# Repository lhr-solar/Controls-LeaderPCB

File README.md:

# Electronics : SCH/PCB
Contains all schematics and PCB files for the electrical system. Some teams may use the Solar Google Drive to upload their files.

------ 2025 Daybreak Controls Leaderboard ------
Purpose: Run main Controls code and interface with the motor controller and other systems through CAN.
Mouser link BOM: <to come>
List of components taking up volume outside of board dimensions
- Molex connectors along the entire perimeter (and one slightly inside) of the board
- Pin headers on the board
LEDs:
- Cruise controls is on
- Controls has a fault
- BPS has sent a fault
- Motor controller sent a fault
- Array precharge bypass contactor pin is high
- Motor precharge bypass contactor pin is high
- Motor contactor pin is high
-

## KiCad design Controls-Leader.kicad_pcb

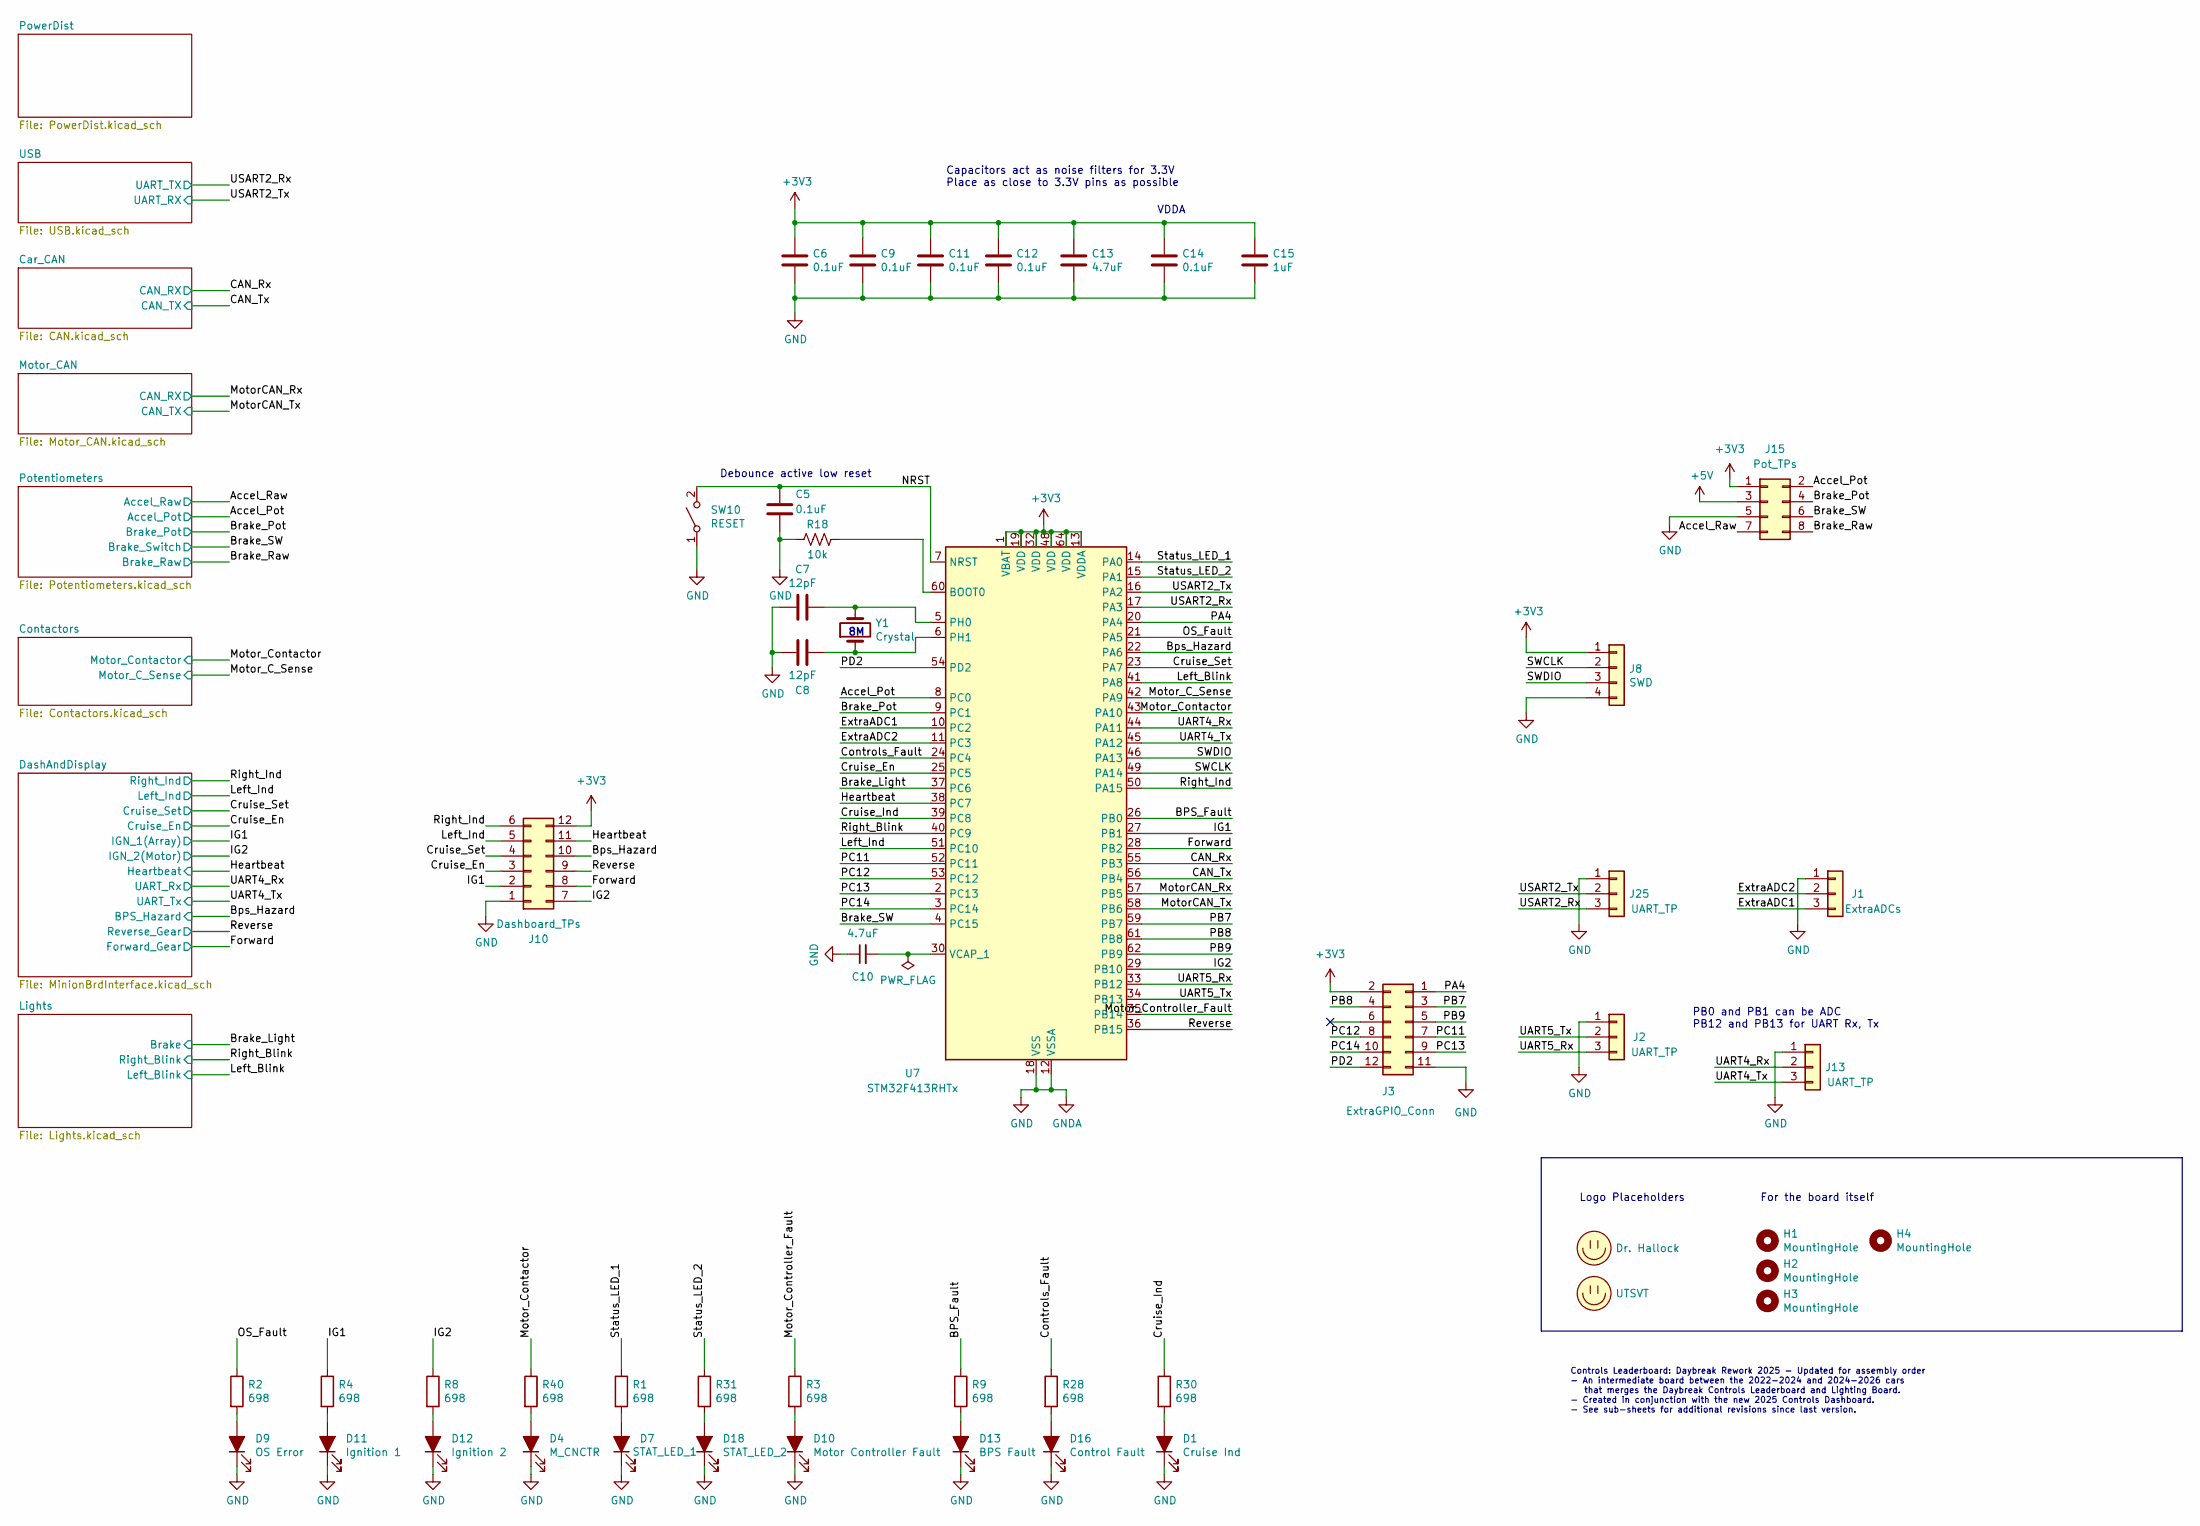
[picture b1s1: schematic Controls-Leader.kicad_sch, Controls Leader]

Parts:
C5, C6, C9, C11, C12, C14: 0.1uF; C_0805_2012Metric; Mouser Part Number 80-C0805C104M5R
C7, C8: 12pF; C_0805_2012Metric; Mouser Part Number 80-C0805C120K5HACTU
C10, C13: 4.7uF; C_0805_2012Metric; Mouser Part Number 81-GRM219R6YA475KA3D
C15: 1uF; C_0805_2012Metric; JLCPCB# C28323
D1: Cruise Ind; LED_0805_2012Metric; Mouser Part Number 604-APTD2012LCGCK
D4: M_CNCTR; LED_0805_2012Metric; Mouser Part Number 604-APTD2012LCGCK
D7: STAT_LED_1; LED_0805_2012Metric; Mouser Part Number 604-APTD2012LCGCK
D9: OS Error; LED_0805_2012Metric; Mouser Part Number 604-APTD2012LCGCK
D10: Motor Controller Fault; LED_0805_2012Metric; Mouser Part Number 604-APTD2012LCGCK
D11: Ignition 1; LED_0805_2012Metric; Mouser Part Number 604-APTD2012LCGCK
D12: Ignition 2; LED_0805_2012Metric; Mouser Part Number 604-APTD2012LCGCK
D13: BPS Fault; LED_0805_2012Metric; Mouser Part Number 604-APTD2012LCGCK
D16: Control Fault; LED_0805_2012Metric; Mouser Part Number 604-APTD2012LCGCK
D18: STAT_LED_2; LED_0805_2012Metric; Mouser Part Number 604-APTD2012LCGCK
H1, H2, H3, H4: MountingHole; MountingHole_3mm
J1: ExtraADCs; PinHeader_1x03_P2.54mm_Vertical
J2, J13, J25: UART_TP; PinHeader_1x03_P2.54mm_Vertical
J3: ExtraGPIO_Conn; PinHeader_2x06_P2.54mm_Vertical
J8: SWD; PinHeader_1x04_P2.54mm_Vertical
J10: Dashboard_TPs; PinHeader_2x06_P2.54mm_Vertical
J15: Pot_TPs; PinHeader_2x04_P2.54mm_Vertical
LOGO1: Dr. Hallock; Hallock_Image
LOGO2: UTSVT; UTSVT_Logo_Symbol
R1, R2, R3, R4, R8, R9, R28, R30, R31, R40: 698; R_0805_2012Metric; Mouser Part Number 652-CR0805FX-6980ELF
R18: 10k; R_0805_2012Metric; Mouser Part Number 71-CRCW080510K0FKEAC
SW10: RESET; SW_SPST_B3SL-1002P; Mouser Part Number 653-B3SL-1002P
U7: STM32F413RHTx; LQFP-64_10x10mm_P0.5mm; Mouser Part Number 511-STM32F413RHT6
Y1: Crystal; Crystal_SMD_TXC_7A-2Pin_5x3.2mm; JLCPCB# C115962

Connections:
+3V3: C6.1, C9.1, C11.1, C12.1, C13.1, C14.1, C15.1, J3.2, J8.1, J10.12, J15.1, U7.1 (VBAT), U7.13 (VDDA), U7.19 (VDD), U7.32 (VDD), U7.48 (VDD), U7.64 (VDD); also elsewhere on the board
+5V: J15.3; also elsewhere on the board
/Accel_Pot: J15.2, U7.8 (PC0); also elsewhere on the board
/Accel_Raw: J15.7; also elsewhere on the board
/BPS_Fault: R9.1, U7.26 (PB0)
/Bps_Hazard: J10.10, U7.22 (PA6); also elsewhere on the board
/Brake_Light: U7.37 (PC6); also elsewhere on the board
/Brake_Pot: J15.4, U7.9 (PC1); also elsewhere on the board
/Brake_Raw: J15.8; also elsewhere on the board
/Brake_SW: J15.6, U7.4 (PC15); also elsewhere on the board
/CAN_Rx: U7.55 (PB3); also elsewhere on the board
/CAN_Tx: U7.56 (PB4); also elsewhere on the board
/Controls_Fault: R28.1, U7.24 (PC4)
/Cruise_En: J10.3, U7.25 (PC5); also elsewhere on the board
/Cruise_Ind: R30.1, U7.39 (PC8)
/Cruise_Set: J10.4, U7.23 (PA7); also elsewhere on the board
/ExtraADC1: J1.3, U7.10 (PC2)
/ExtraADC2: J1.2, U7.11 (PC3)
/Forward: J10.8, U7.28 (PB2); also elsewhere on the board
/Heartbeat: J10.11, U7.38 (PC7); also elsewhere on the board
/IG1: J10.2, R4.1, U7.27 (PB1); also elsewhere on the board
/IG2: J10.7, R8.1, U7.29 (PB10); also elsewhere on the board
/Left_Blink: U7.41 (PA8); also elsewhere on the board
/Left_Ind: J10.5, U7.51 (PC10); also elsewhere on the board
/MotorCAN_Rx: U7.57 (PB5); also elsewhere on the board
/MotorCAN_Tx: U7.58 (PB6); also elsewhere on the board
/Motor_C_Sense: U7.42 (PA9); also elsewhere on the board
/Motor_Contactor: R40.1, U7.43 (PA10); also elsewhere on the board
/Motor_Controller_Fault: R3.1, U7.35 (PB14)
/NRST: C5.1, SW10.2 (B), U7.7 (NRST)
/OS_Fault: R2.1, U7.21 (PA5)
/PA4: J3.1, U7.20 (PA4)
/PB7: J3.3, U7.59 (PB7)
/PB8: J3.4, U7.61 (PB8)
/PB9: J3.5, U7.62 (PB9)
/PC11: J3.7, U7.52 (PC11)
/PC12: J3.8, U7.53 (PC12)
/PC13: J3.9, U7.2 (PC13)
/PC14: J3.10, U7.3 (PC14)
/PD2: J3.12, U7.54 (PD2)
/Reverse: J10.9, U7.36 (PB15); also elsewhere on the board
/Right_Blink: U7.40 (PC9); also elsewhere on the board
/Right_Ind: J10.6, U7.50 (PA15); also elsewhere on the board
/SWCLK: J8.2, U7.49 (PA14)
/SWDIO: J8.3, U7.46 (PA13)
/Status_LED_1: R1.1, U7.14 (PA0)
/Status_LED_2: R31.1, U7.15 (PA1)
/UART4_Rx: J13.2, U7.44 (PA11); also elsewhere on the board
/UART4_Tx: J13.3, U7.45 (PA12); also elsewhere on the board
/UART5_Rx: J2.3, U7.33 (PB12)
/UART5_Tx: J2.2, U7.34 (PB13)
/USART2_Rx: J25.3, U7.17 (PA3); also elsewhere on the board
/USART2_Tx: J25.2, U7.16 (PA2); also elsewhere on the board
GND: C5.2, C6.2, C7.2, C8.2, C9.2, C10.1, C11.2, C12.2, C13.2, C14.2, C15.2, D1.1 (K), D4.1 (K), D7.1 (K), D9.1 (K), D10.1 (K), D11.1 (K), D12.1 (K), D13.1 (K), D16.1 (K), D18.1 (K), J1.1, J2.1, J3.11, J8.4, J10.1, J13.1, J15.5, J25.1, R18.2, SW10.1 (A), U7.12 (VSSA), U7.18 (VSS), U7.31 (VSS), U7.47 (VSS), U7.63 (VSS); also elsewhere on the board
unnamed: D1.2 (A), R30.2
unnamed: D4.2 (A), R40.2
unnamed: D7.2 (A), R1.2
unnamed: D9.2 (A), R2.2
unnamed: D10.2 (A), R3.2
unnamed: D11.2 (A), R4.2
unnamed: D12.2 (A), R8.2
unnamed: D13.2 (A), R9.2
unnamed: D16.2 (A), R28.2
unnamed: D18.2 (A), R31.2
unnamed: R18.1, U7.60 (BOOT0)
unnamed: C7.1, U7.5 (PH0), Y1.2
unnamed: C8.1, U7.6 (PH1), Y1.1
unnamed: C10.2, U7.30 (VCAP_1)

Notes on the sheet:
VDDA
PB0 and PB1 can be ADC PB12 and PB13 for UART Rx, Tx
Debounce active low reset
Logo Placeholders
Controls Leaderboard: Daybreak Rework 2025 - Updated for assembly order - An intermediate board between the 2022-2024 and 2024-2026 cars that merges the Daybreak Controls Leaderboard and Lighting Board. - Created in conjunction with the new 2025 Controls Dashboard. - See sub-sheets for additional r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
Capacitors act as noise filters for 3.3V Place as close to 3.3V pins as possible
For the board itself

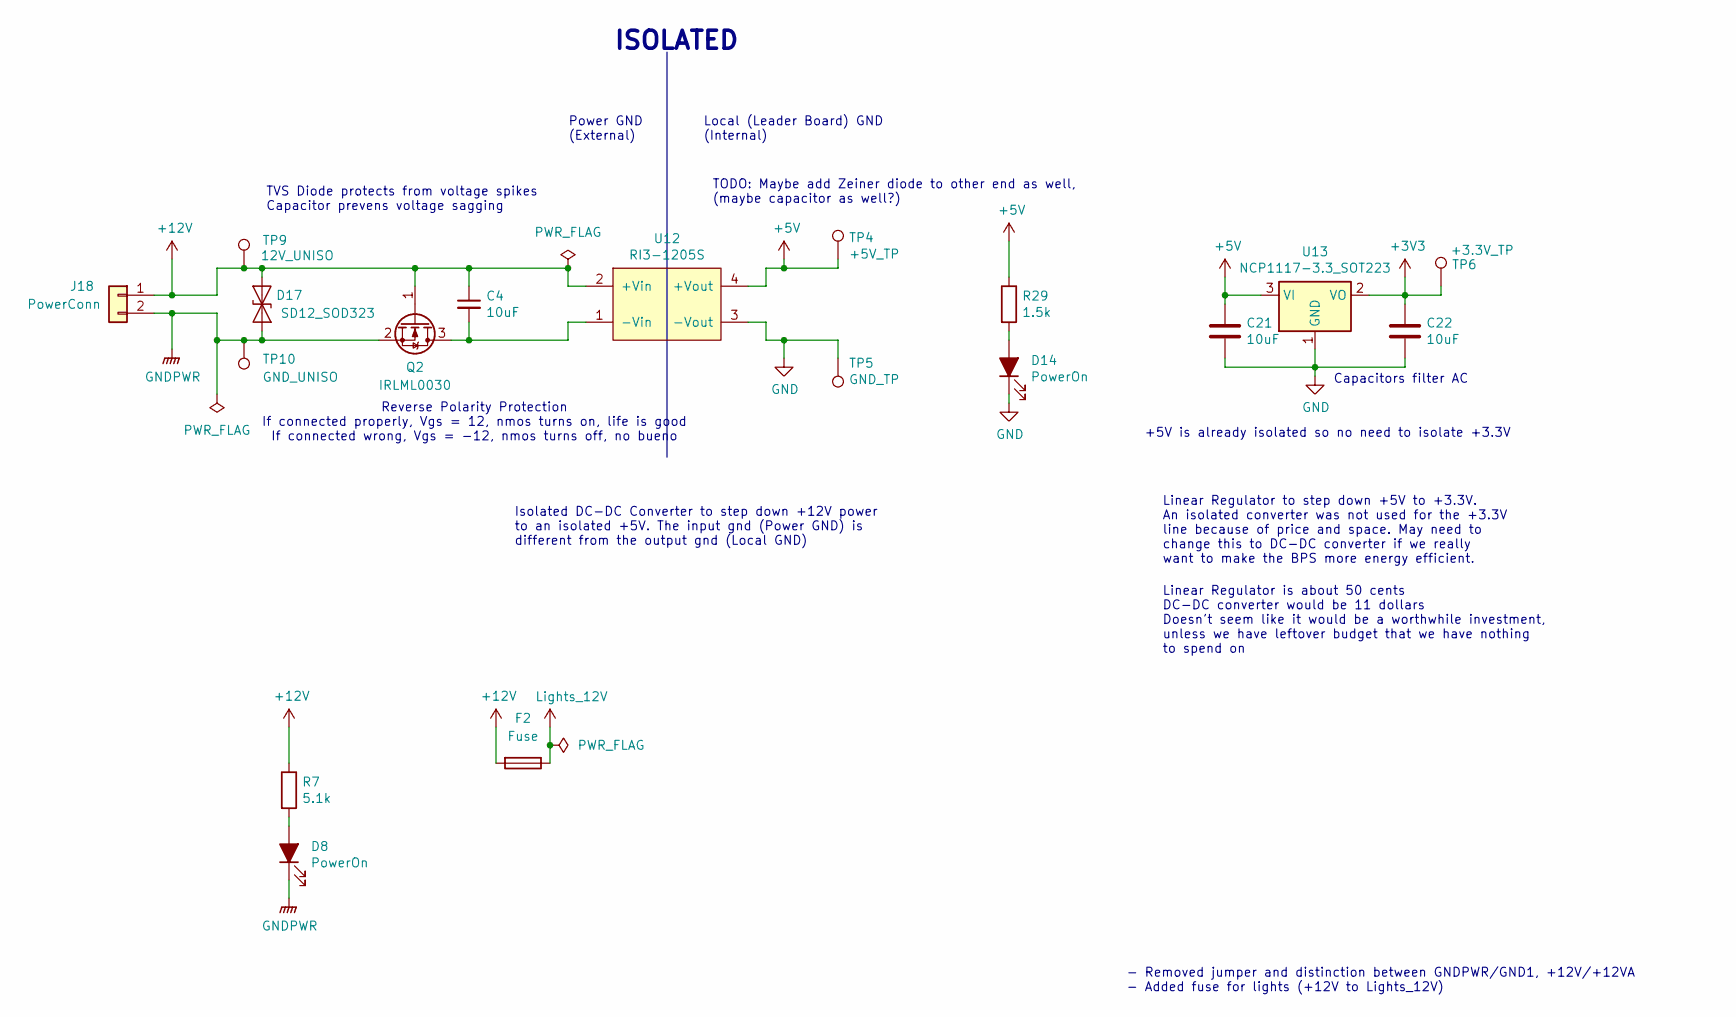
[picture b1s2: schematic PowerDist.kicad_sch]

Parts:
C4, C21, C22: 10uF; C_0805_2012Metric; Mouser Part Number 963-TMK212BBJ106MGHT
D8, D14: PowerOn; LED_0805_2012Metric; Mouser Part Number 604-APTD2012LCGCK
D17: SD12_SOD323; D_SOD-323; JLCPCB# C85198
F2: Fuse; Fuse_1206_3216Metric; Mouser Part Number 576-0440003.WR
J18: PowerConn; Molex_MicroFit3.0_1x2xP3.00mm_PolarizingPeg_Vertical
Q2: IRLML0030; SOT-23; JLCPCB# C67272
R7: 5.1k; R_0805_2012Metric; JLCPCB# C27834
R29: 1.5k; R_0805_2012Metric; Mouser Part Number 71-CRCW08051K50JNEB
TP4: +5V_TP; TestPoint_Keystone_5005-5009_Compact
TP5: GND_TP; TestPoint_Keystone_5005-5009_Compact
TP6: +3.3V_TP; TestPoint_Keystone_5005-5009_Compact
TP9: 12V_UNISO; TestPoint_Keystone_5005-5009_Compact
TP10: GND_UNISO; TestPoint_Keystone_5005-5009_Compact
U12: RI3-1205S; RI3_DC_Converter; Mouser Part Number 919-RI3-1205S
U13: NCP1117-3.3_SOT223; SOT-223-3_TabPin2; Mouser Part Number 863-NCP1117ST33T3G

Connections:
+3V3: C22.1, TP6.1, U13.2 (VO); also elsewhere on the board
+5V: C21.1, R29.1, TP4.1, U12.4 (+Vout), U13.3 (VI); also elsewhere on the board
+12V: C4.1, D17.2 (A2), F2.2, J18.1, Q2.1 (G), R7.1, TP9.1, U12.2 (+Vin); also elsewhere on the board
GND: C21.2, C22.2, D14.1 (K), TP5.1, U12.3 (-Vout), U13.1 (GND); also elsewhere on the board
GNDPWR: D8.1 (K), D17.1 (A1), J18.2, Q2.2 (S), TP10.1; also elsewhere on the board
Lights_12V: F2.1; also elsewhere on the board
unnamed: D8.2 (A), R7.2
unnamed: D14.2 (A), R29.2
unnamed: C4.2, Q2.3 (D), U12.1 (-Vin)

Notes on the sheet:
Isolated DC-DC Converter to step down +12V power to an isolated +5V. The input gnd (Power GND) is different from the output gnd (Local GND)
TODO: Maybe add Zeiner diode to other end as well, (maybe capacitor as well?)
Linear Regulator to step down +5V to +3.3V. An isolated converter was not used for the +3.3V line because of price and space. May need to change this to DC-DC converter if we really want to make the BPS more energy efficient.
Local (Leader Board) GND (Internal)
Linear Regulator is about 50 cents DC-DC converter would be 11 dollars Doesn't seem like it would be a worthwhile investment, unless we have leftover budget that we have nothing to spend on
+5V is already isolated so no need to isolate +3.3V
Power GND (External)
ISOLATED
TVS Diode protects from voltage spikes Capacitor prevens voltage sagging
Capacitors filter AC
- Removed jumper and distinction between GNDPWR/GND1, +12V/+12VA - Added fuse for lights (+12V to Lights_12V)
Reverse Polarity Protection If connected properly, Vgs = 12, nmos turns on, life is good If connected wrong, Vgs = -12, nmos turns off, no bueno

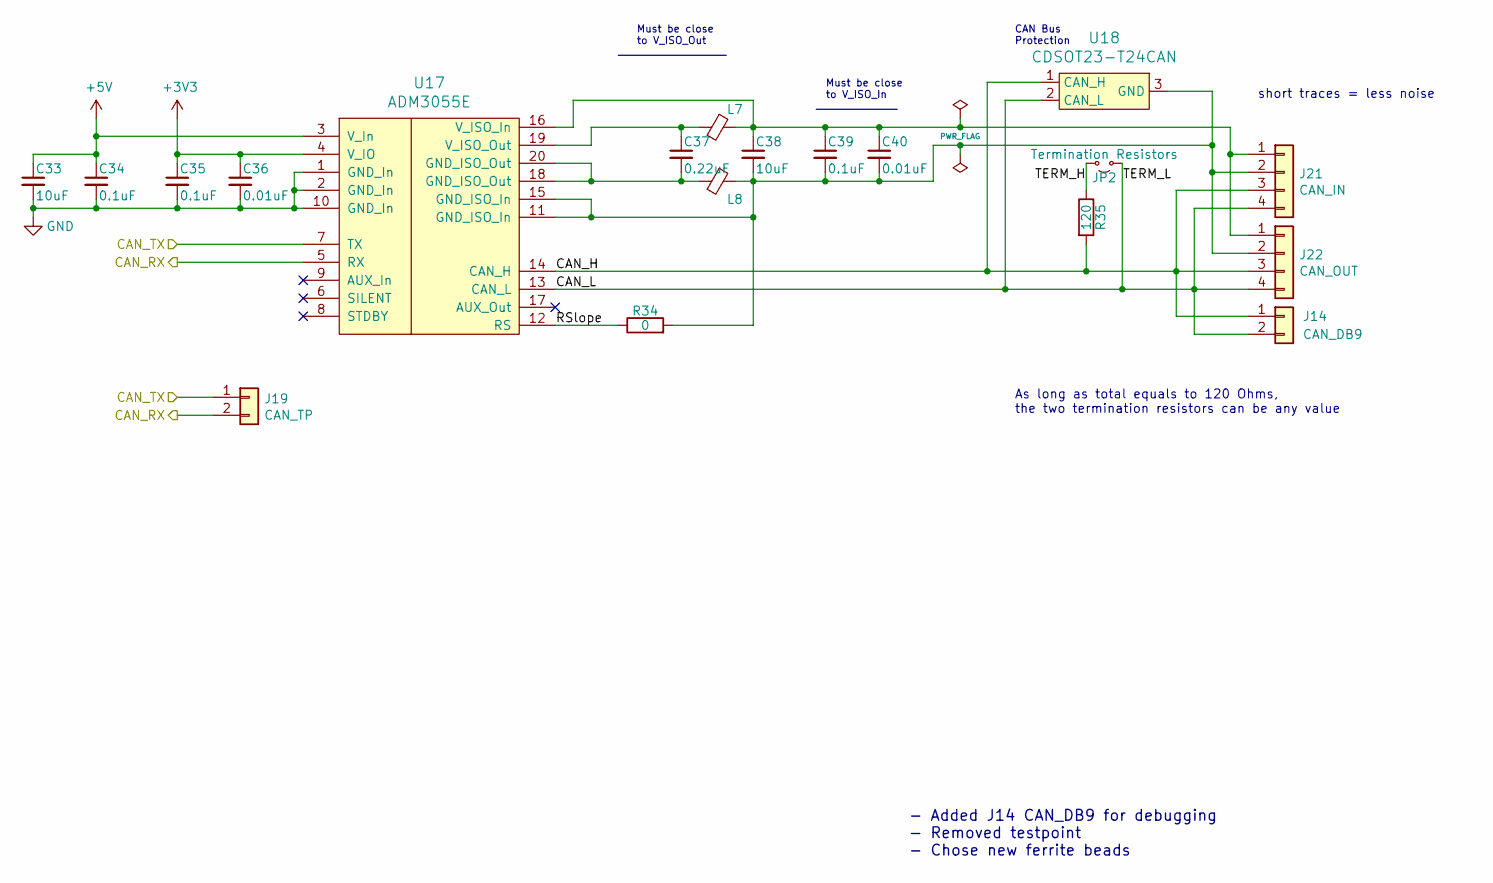
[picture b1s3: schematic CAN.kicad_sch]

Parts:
C33, C38: 10uF; C_0805_2012Metric; Mouser Part Number 963-TMK212BBJ106MGHT
C34, C35, C39: 0.1uF; C_0805_2012Metric; Mouser Part Number 80-C0805C104M5R
C36, C40: 0.01uF; C_0805_2012Metric; JLCPCB# C1710
C37: 0.22uF; C_0805_2012Metric; Mouser Part Number 80-C0805C224J1RECTU
J14: CAN_DB9; Molex_Micro-Fit_3.0_43650-0215_1x02_P3.00mm_Vertical
J19: CAN_TP; PinHeader_1x02_P2.54mm_Vertical
J21: CAN_IN; Molex_MicroFit3.0_1x4xP3.00mm_PolarizingPeg_Vertical
J22: CAN_OUT; Molex_MicroFit3.0_1x4xP3.00mm_PolarizingPeg_Vertical
JP2: Termination Resistors; PinHeader_1x02_P2.54mm_Vertical
L7, L8: 1.8k; L_0805_2012Metric; Mouser Part Number 710-742792090
R34: 0; R_0805_2012Metric; Mouser Part Number 71-CRCW08050000Z0EAC
R35: 120; R_0805_2012Metric; JLCPCB# C17437
U17: ADM3055E; SOIC-20W_7.5x15.4mm_Pitch1.27mm; JLCPCB# C658105
U18: CDSOT23-T24CAN; SOT-23-3; Mouser Part Number 652-CDSOT23-T24CAN

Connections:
+3V3: C35.1, C36.1, U17.4 (V_IO); also elsewhere on the board
+5V: C33.1, C34.1, U17.3 (V_In); also elsewhere on the board
/CAN_Rx: J19.2, U17.5 (RX); also elsewhere on the board
/CAN_Tx: J19.1, U17.7 (TX); also elsewhere on the board
/Car_CAN/CAN_H: J14.1, J21.3, J22.3, R35.2, U17.14 (CAN_H), U18.1 (CAN_H)
/Car_CAN/CAN_L: J14.2, J21.4, J22.4, JP2.1 (A), U17.13 (CAN_L), U18.2 (CAN_L)
/Car_CAN/RSlope: R34.1, U17.12 (RS)
/Car_CAN/TERM_H: JP2.2 (B), R35.1
GND: C33.2, C34.2, C35.2, C36.2, U17.1 (GND_In), U17.2 (GND_In), U17.10 (GND_In); also elsewhere on the board
unnamed: C37.2, L8.2, U17.18 (GND_ISO_Out), U17.20 (GND_ISO_Out)
unnamed: C38.1, C39.1, C40.1, J21.1, J22.1, L7.1, U17.16 (V_ISO_In)
unnamed: C38.2, C39.2, C40.2, J21.2, J22.2, L8.1, R34.2, U17.11 (GND_ISO_In), U17.15 (GND_ISO_In), U18.3 (GND)
unnamed: C37.1, L7.2, U17.19 (V_ISO_Out)

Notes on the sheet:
short traces = less noise
CAN Bus Protection
As long as total equals to 120 Ohms, the two termination resistors can be any value
Must be close to V_ISO_Out
Must be close to V_ISO_In
- Added J14 CAN_DB9 for debugging - Removed testpoint - Chose new ferrite beads

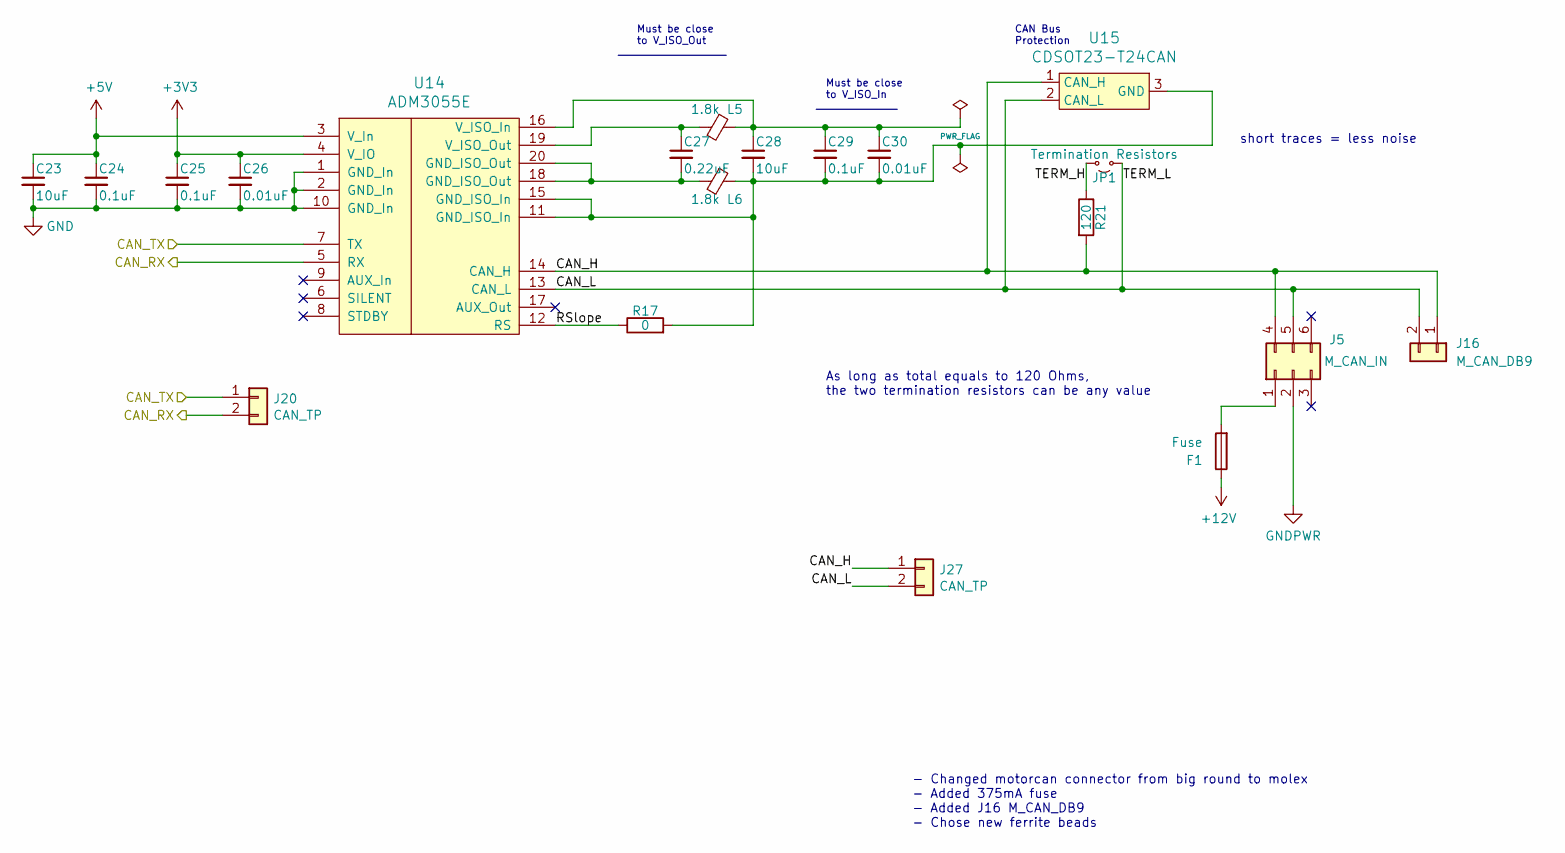
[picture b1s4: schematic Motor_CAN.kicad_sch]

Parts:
C23, C28: 10uF; C_0805_2012Metric; Mouser Part Number 963-TMK212BBJ106MGHT
C24, C25, C29: 0.1uF; C_0805_2012Metric; Mouser Part Number 80-C0805C104M5R
C26, C30: 0.01uF; C_0805_2012Metric; JLCPCB# C1710
C27: 0.22uF; C_0805_2012Metric; Mouser Part Number 80-C0805C224J1RECTU
F1: Fuse; Fuse_1206_3216Metric; Mouser Part Number 576-0440.375WR
J5: M_CAN_IN; Molex_Micro-Fit_3.0_43045-0612_2x03_P3.00mm_Vertical
J16: M_CAN_DB9; Molex_Micro-Fit_3.0_43650-0215_1x02_P3.00mm_Vertical; JLCPCB# C293740
J20, J27: CAN_TP; PinHeader_1x02_P2.54mm_Vertical
JP1: Termination Resistors; PinHeader_1x02_P2.54mm_Vertical
L5, L6: 1.8k; L_0805_2012Metric; Mouser Part Number 710-742792090
R17: 0; R_0805_2012Metric; Mouser Part Number 71-CRCW08050000Z0EAC
R21: 120; R_0805_2012Metric; JLCPCB# C17437
U14: ADM3055E; SOIC-20W_7.5x15.4mm_Pitch1.27mm; JLCPCB# C658104
U15: CDSOT23-T24CAN; SOT-23-3; Mouser Part Number 652-CDSOT23-T24CAN

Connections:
+3V3: C25.1, C26.1, U14.4 (V_IO); also elsewhere on the board
+5V: C23.1, C24.1, U14.3 (V_In); also elsewhere on the board
+12V: F1.1; also elsewhere on the board
/MotorCAN_Rx: J20.2, U14.5 (RX); also elsewhere on the board
/MotorCAN_Tx: J20.1, U14.7 (TX); also elsewhere on the board
/Motor_CAN/CAN_H: J5.4, J16.1, J27.1, R21.2, U14.14 (CAN_H), U15.1 (CAN_H)
/Motor_CAN/CAN_L: J5.5, J16.2, J27.2, JP1.1 (A), U14.13 (CAN_L), U15.2 (CAN_L)
/Motor_CAN/RSlope: R17.1, U14.12 (RS)
/Motor_CAN/TERM_H: JP1.2 (B), R21.1
GND: C23.2, C24.2, C25.2, C26.2, U14.1 (GND_In), U14.2 (GND_In), U14.10 (GND_In); also elsewhere on the board
GNDPWR: J5.2; also elsewhere on the board
unnamed: C27.2, L6.2, U14.18 (GND_ISO_Out), U14.20 (GND_ISO_Out)
unnamed: F1.2, J5.1
unnamed: C28.1, C29.1, C30.1, L5.1, U14.16 (V_ISO_In)
unnamed: C27.1, L5.2, U14.19 (V_ISO_Out)
unnamed: C28.2, C29.2, C30.2, L6.1, R17.2, U14.11 (GND_ISO_In), U14.15 (GND_ISO_In), U15.3 (GND)

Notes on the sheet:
Must be close to V_ISO_Out
Must be close to V_ISO_In
short traces = less noise
As long as total equals to 120 Ohms, the two termination resistors can be any value
- Changed motorcan connector from big round to molex - Added 375mA fuse - Added J16 M_CAN_DB9 - Chose new ferrite beads
CAN Bus Protection

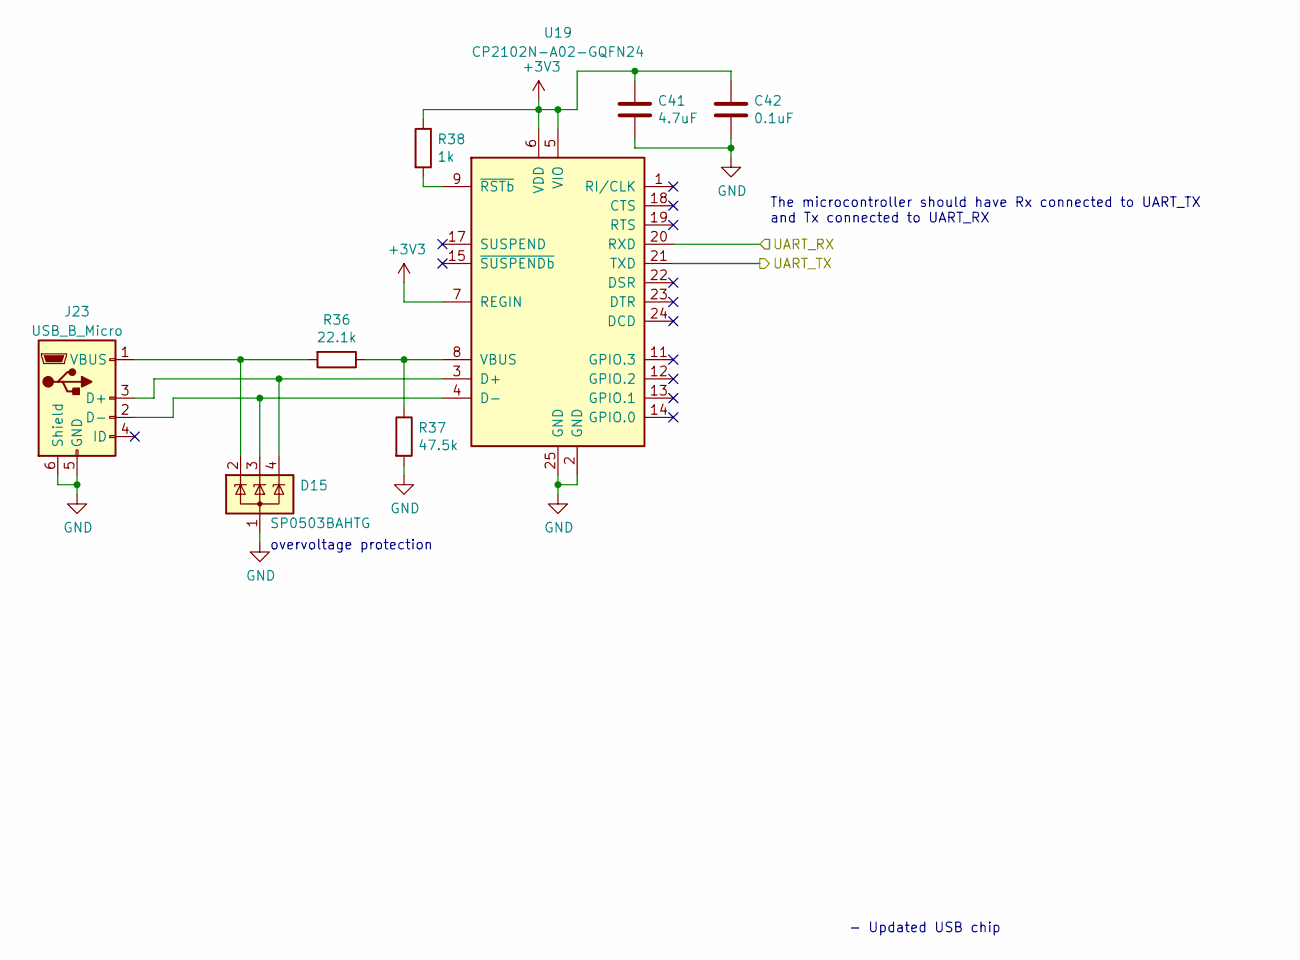
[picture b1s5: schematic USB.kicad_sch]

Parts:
C41: 4.7uF; C_0805_2012Metric; Mouser Part Number 81-GRM219R6YA475KA3D
C42: 0.1uF; C_0805_2012Metric; Mouser Part Number 80-C0805C104M5R
D15: SP0503BAHTG; SOT-143; Mouser Part Number 576-SP0503BAHTG
J23: USB_B_Micro; USB_Micro-B_Molex-105017-0001; Mouser Part Number 538-105017-1001
R36: 22.1k; R_0805_2012Metric; Mouser Part Number 71-CRCW0805-22.1K-E3
R37: 47.5k; R_0805_2012Metric; Mouser Part Number 71-CRCW0805-47.5K-E3
R38: 1k; R_0805_2012Metric; Mouser Part Number 71-CRCW08051K00FKEAC
U19: CP2102N-A02-GQFN24; QFN-24-1EP_4x4mm_P0.5mm_EP2.6x2.6mm; Mouser Part Number 634-CP2102NA01GQFN24

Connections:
+3V3: C41.1, C42.1, R38.1, U19.5 (VIO), U19.6 (VDD), U19.7 (REGIN); also elsewhere on the board
/USART2_Rx: U19.21 (TXD); also elsewhere on the board
/USART2_Tx: U19.20 (RXD); also elsewhere on the board
GND: C41.2, C42.2, D15.1 (A), J23.5 (GND), J23.6 (Shield), R37.2, U19.2 (GND), U19.25 (GND); also elsewhere on the board
unnamed: D15.4 (K), J23.3 (D+), U19.3 (D+)
unnamed: D15.3 (K), J23.2 (D-), U19.4 (D-)
unnamed: D15.2 (K), J23.1 (VBUS), R36.2
unnamed: R36.1, R37.1, U19.8 (VBUS)
unnamed: R38.2, U19.9 (~RSTb)

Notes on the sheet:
- Updated USB chip
The microcontroller should have Rx connected to UART_TX and Tx connected to UART_RX
overvoltage protection

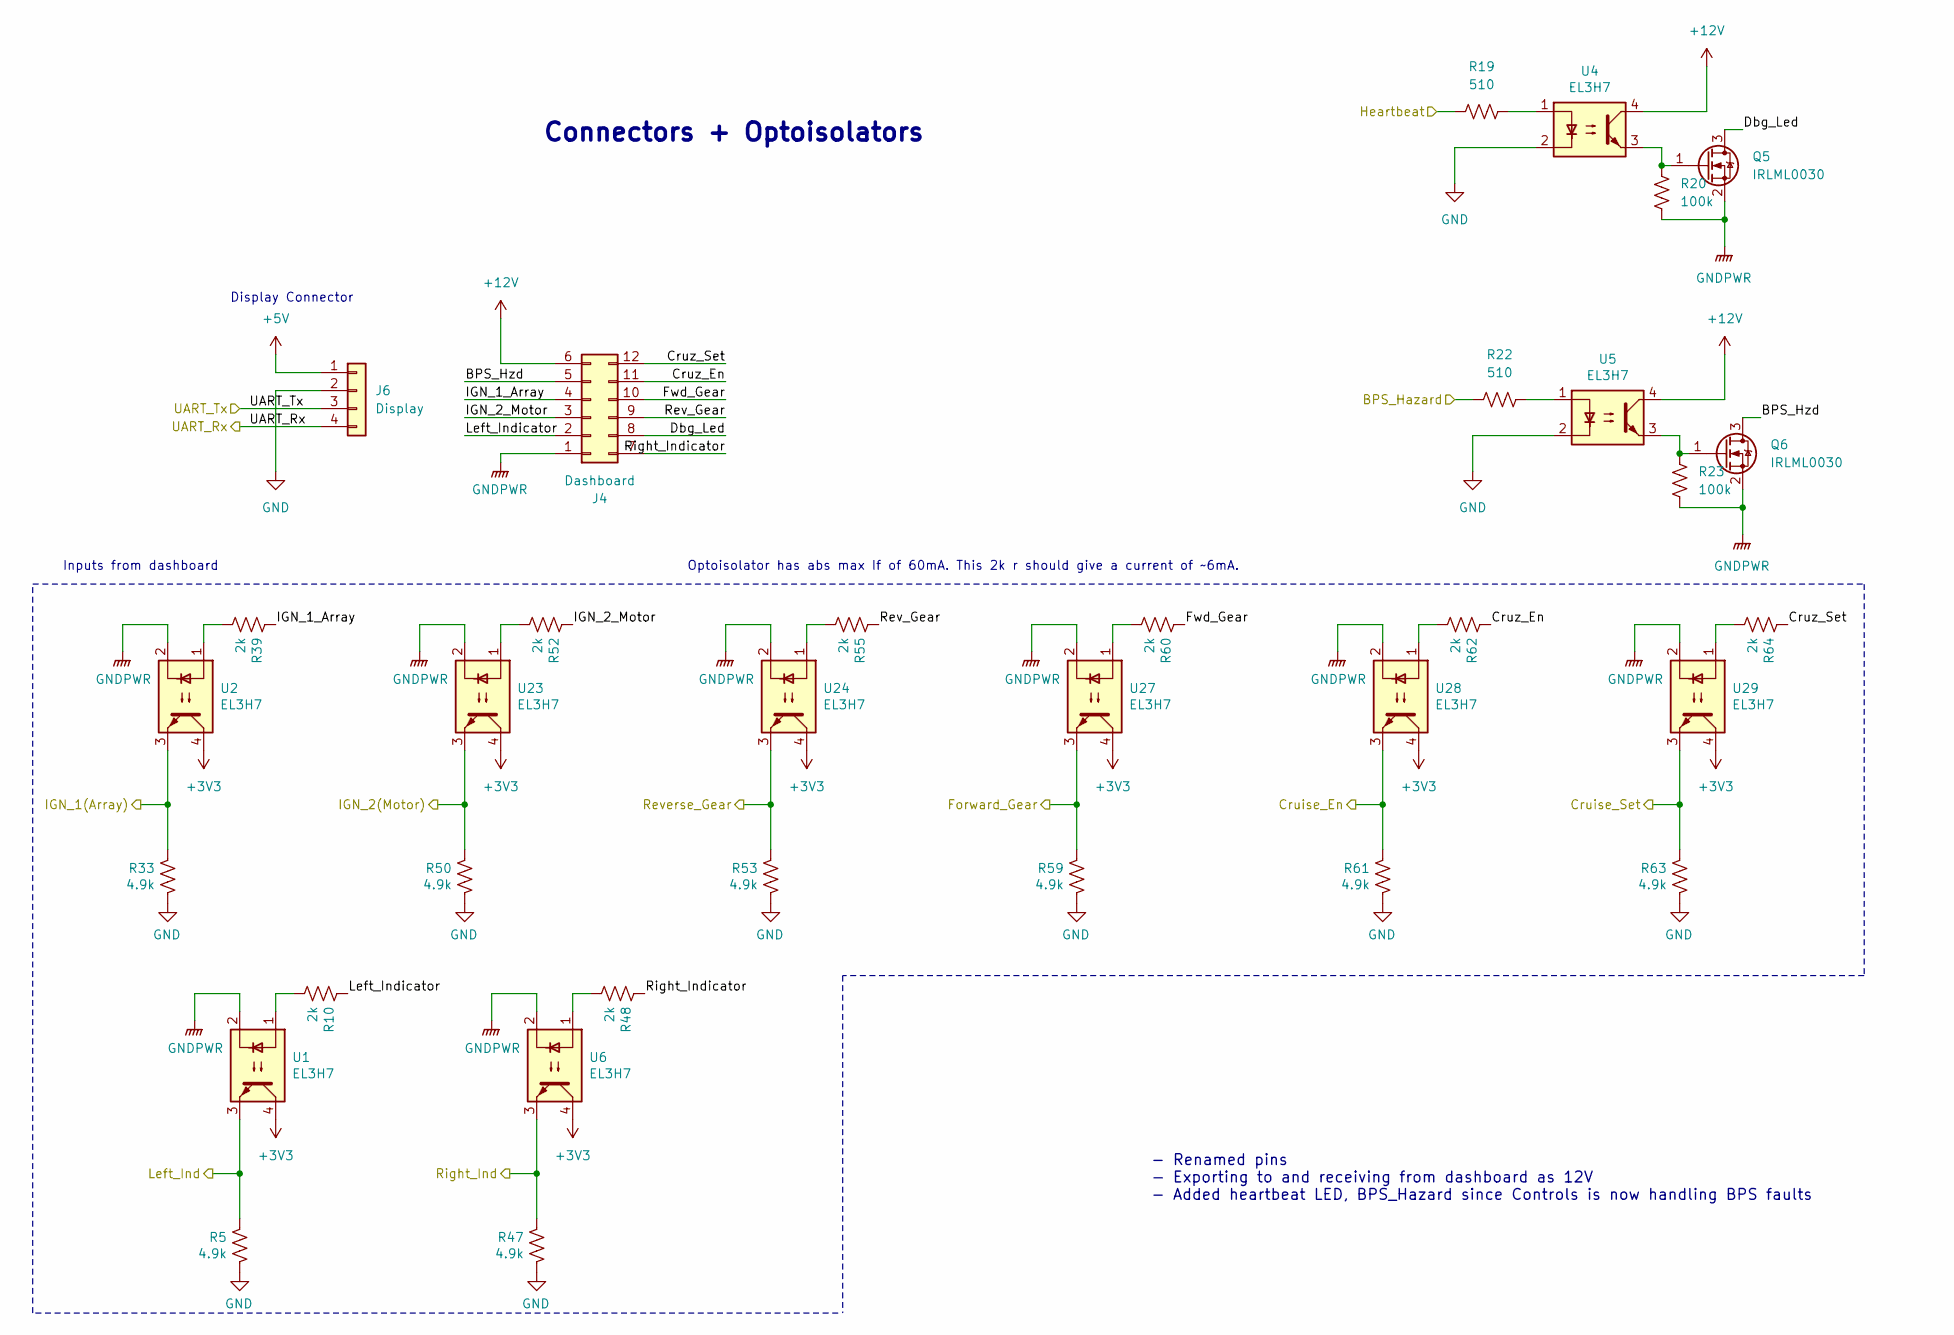
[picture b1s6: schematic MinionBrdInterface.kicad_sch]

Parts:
J4: Dashboard; Molex_MicroFit3.0_2x6xP3.00mm_PolarizingPeg_Vertical
J6: Display; Molex_Micro-Fit_3.0_43650-0415_1x04_P3.00mm_Vertical
Q5, Q6: IRLML0030; SOT-23; JLCPCB# C5364304
R5, R33, R47, R50, R53, R59, R61, R63: 4.9k; R_0805_2012Metric; Mouser Part Number 71-CRCW08054K99FKEAC
R10, R39, R48, R52, R55, R60, R62, R64: 2k; R_0805_2012Metric; Mouser Part Number 71-CRCW08052K00FKEC
R19, R22: 510; R_0805_2012Metric; Mouser Part Number 71-CRCW0805510RFKEAC
R20, R23: 100k; R_0805_2012Metric; Mouser Part Number 71-CRCW0805100KFKEAC
U1, U2, U4, U5, U6, U23, U24, U27, U28, U29: EL3H7; SSOP-4_4.4x2.6mm_P1.27mm; Mouser Part Number 638-EL3H7DTAVG

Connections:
+3V3: U1.4, U2.4, U6.4, U23.4, U24.4, U27.4, U28.4, U29.4; also elsewhere on the board
+5V: J6.1; also elsewhere on the board
+12V: J4.6, U4.4, U5.4; also elsewhere on the board
/Bps_Hazard: R22.1; also elsewhere on the board
/Cruise_En: R61.1, U28.3; also elsewhere on the board
/Cruise_Set: R63.1, U29.3; also elsewhere on the board
/DashAndDisplay/BPS_Hzd: J4.5, Q6.3 (D)
/DashAndDisplay/Cruz_En: J4.11, R62.1
/DashAndDisplay/Cruz_Set: J4.12, R64.1
/DashAndDisplay/Dbg_Led: J4.8, Q5.3 (D)
/DashAndDisplay/Fwd_Gear: J4.10, R60.1
/DashAndDisplay/IGN_1_Array: J4.4, R39.1
/DashAndDisplay/IGN_2_Motor: J4.3, R52.1
/DashAndDisplay/Left_Indicator: J4.2, R10.1
/DashAndDisplay/Rev_Gear: J4.9, R55.1
/DashAndDisplay/Right_Indicator: J4.7, R48.1
/Forward: R59.1, U27.3; also elsewhere on the board
/Heartbeat: R19.1; also elsewhere on the board
/IG1: R33.1, U2.3; also elsewhere on the board
/IG2: R50.1, U23.3; also elsewhere on the board
/Left_Ind: R5.1, U1.3; also elsewhere on the board
/Reverse: R53.1, U24.3; also elsewhere on the board
/Right_Ind: R47.1, U6.3; also elsewhere on the board
/UART4_Rx: J6.4; also elsewhere on the board
/UART4_Tx: J6.3; also elsewhere on the board
GND: J6.2, R5.2, R33.2, R47.2, R50.2, R53.2, R59.2, R61.2, R63.2, U4.2, U5.2; also elsewhere on the board
GNDPWR: J4.1, Q5.2 (S), Q6.2 (S), R20.2, R23.2, U1.2, U2.2, U6.2, U23.2, U24.2, U27.2, U28.2, U29.2; also elsewhere on the board
unnamed: Q5.1 (G), R20.1, U4.3
unnamed: Q6.1 (G), R23.1, U5.3
unnamed: R10.2, U1.1
unnamed: R19.2, U4.1
unnamed: R22.2, U5.1
unnamed: R39.2, U2.1
unnamed: R48.2, U6.1
unnamed: R52.2, U23.1
unnamed: R55.2, U24.1
unnamed: R60.2, U27.1
unnamed: R62.2, U28.1
unnamed: R64.2, U29.1

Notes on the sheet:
- Renamed pins - Exporting to and receiving from dashboard as 12V - Added heartbeat LED, BPS_Hazard since Controls is now handling BPS faults
Connectors + Optoisolators
Inputs from dashboard
Display Connector
Optoisolator has abs max If of 60mA. This 2k r should give a current of ~6mA.

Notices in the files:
parts and their libraries:
Copyright 2016 Accelerated Designs. All rights reserved.
